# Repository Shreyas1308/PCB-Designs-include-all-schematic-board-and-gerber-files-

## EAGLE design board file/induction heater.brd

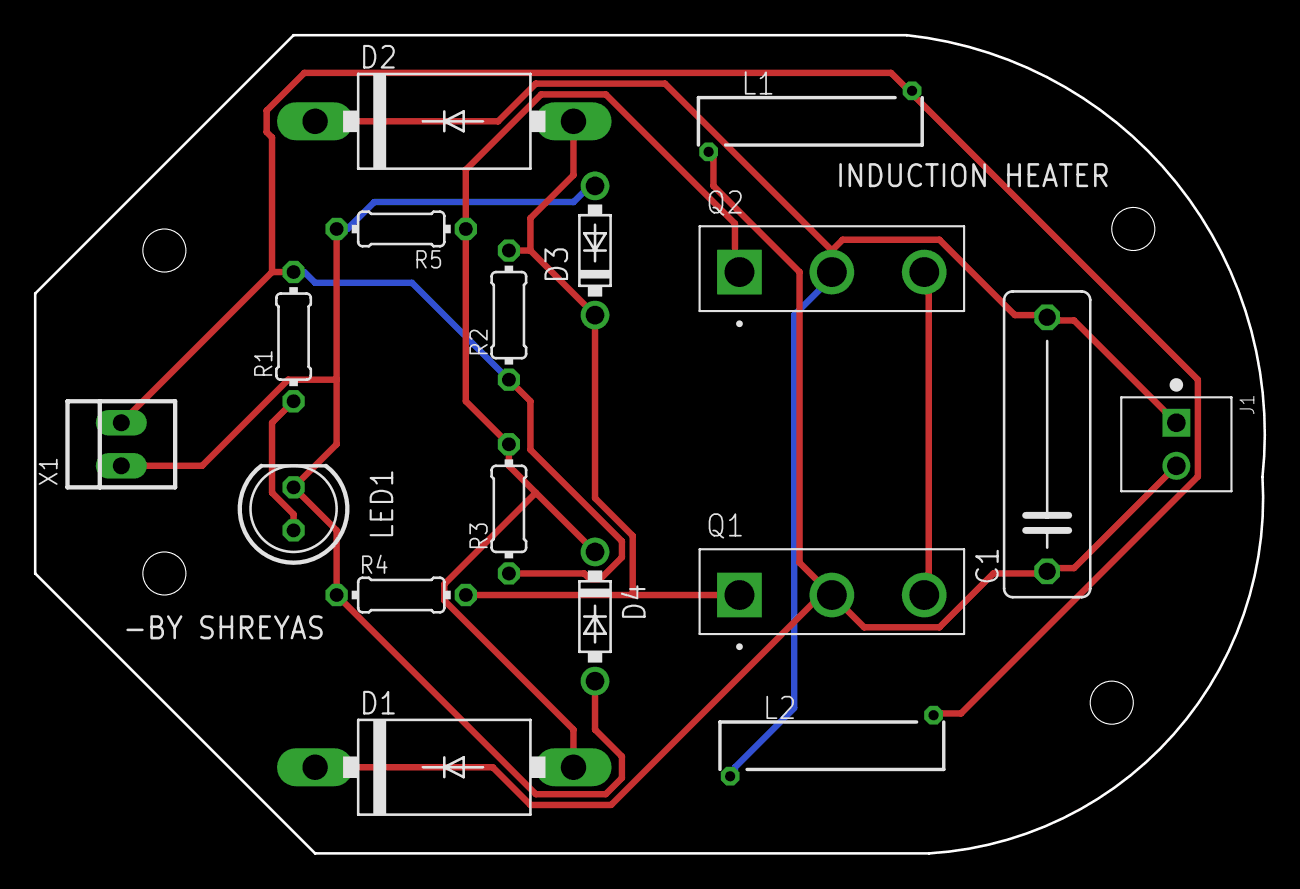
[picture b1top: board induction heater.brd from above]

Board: 2 copper layers, 72.5 x 48.3 mm, 17 parts (0 on the bottom side), 8 nets.

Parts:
C1: 33uF; C150-054X183
D1, D2: 1N5400; DO201-15
D3, D4: 1N4742DO41-7.6; DO41-7.6
J1: 282834-2; CONN_282834-2
L1, L2: Z15/4
LED1: LED5MM
Q1, Q2: IRFP260N; TO545P1560X500X2460-3
R1: 4.7K; 0204/7
R2, R3: 470ohm; 0204/7
R4, R5: 10K; 0204/7
X1: 22-23-2021

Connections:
unnamed: LED1.A, R1.1
unnamed: D2.A, D3.C, Q1.1, R2.2, R4.2
unnamed: D3.A, D4.A, LED1.K, R4.1, R5.2, X1.1
unnamed: Q1.3, Q2.3
unnamed: D1.A, D4.C, Q2.1, R3.2, R5.1
unnamed: C1.2, D2.C, J1.1, L2.1, Q2.2
unnamed: L1.2, L2.2, R1.2, R2.1, R3.1, X1.2
unnamed: C1.1, D1.C, J1.2, L1.1, Q1.2
